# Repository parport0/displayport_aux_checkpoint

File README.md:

# displayport\_aux\_checkpoint 

An RP2040-powered box to be plugged between your computer and the monitor.

See also:

* [dvi_i2c_checkpoint](https://github.com/parport0/dvi_i2c_checkpoint)
* [ddcci_injector](https://github.com/parport0/ddcci_injector)
* [ddcci_dongle](https://github.com/parport0/ddcci_dongle)

Made to be manufactured at JLCPCB,

* JLC04161H-7628
* NanYa NP-155F

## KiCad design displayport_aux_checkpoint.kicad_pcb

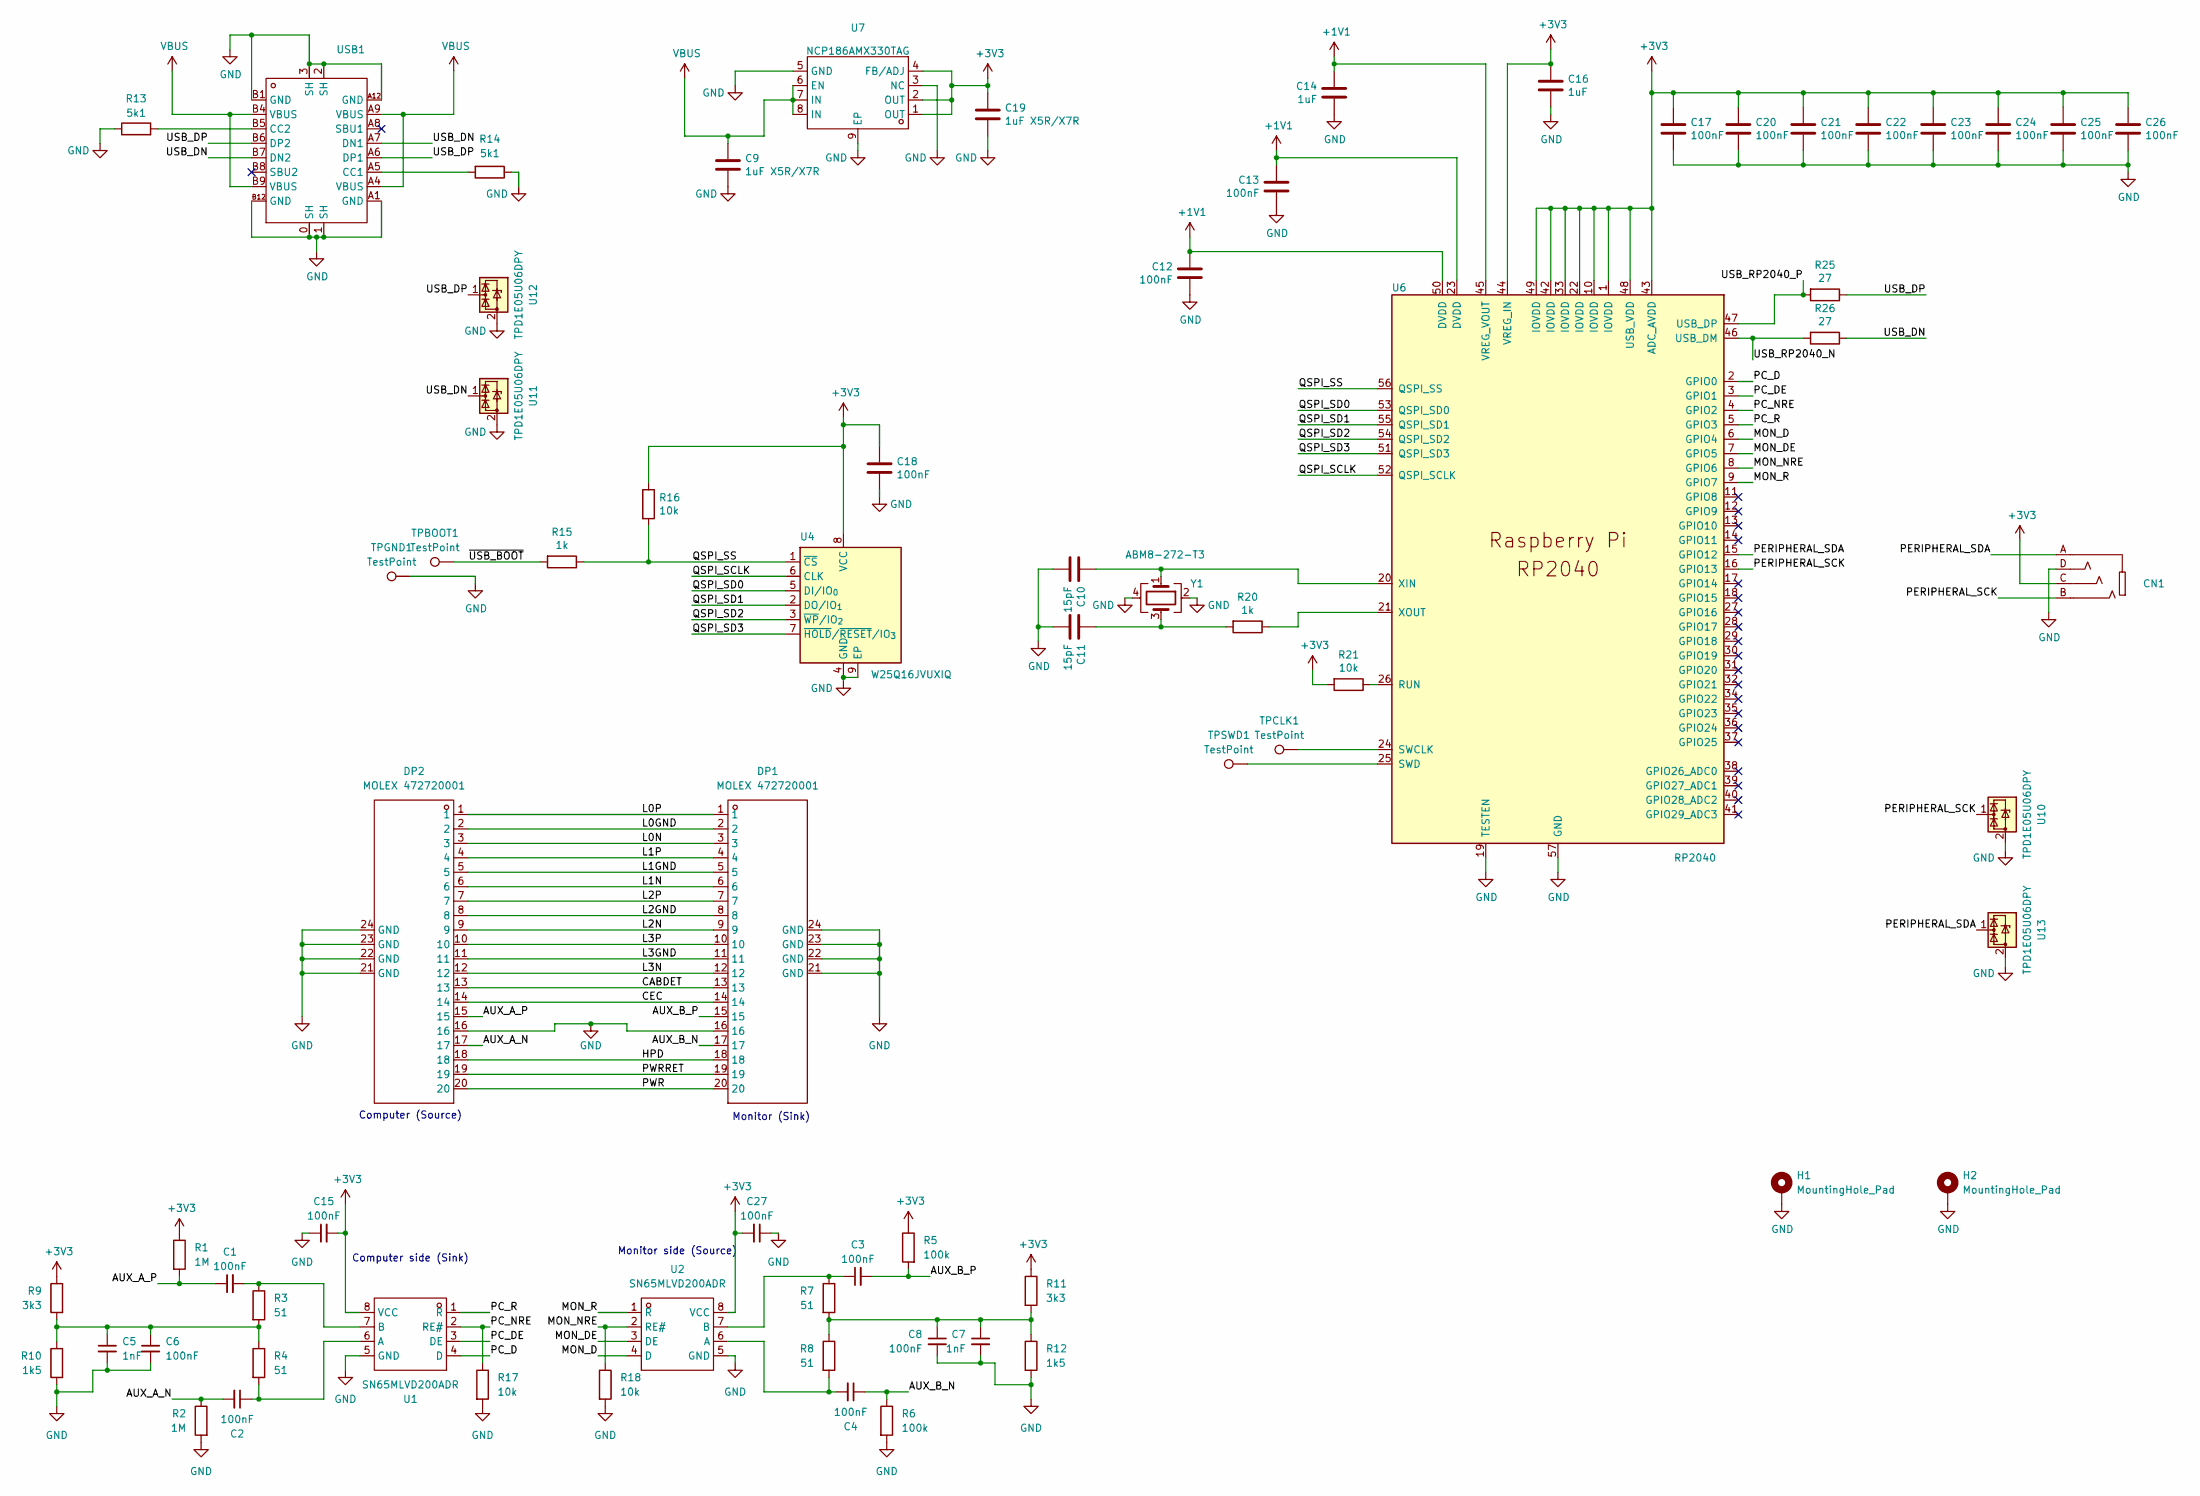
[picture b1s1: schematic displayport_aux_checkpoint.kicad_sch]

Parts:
C1, C2, C3, C4, C15, C27: 100nF; C_0402_1005Metric; Voltage 1kV; Tolerance 100%; LCSC Part C105883
C5, C7: 1nF; C_0402_1005Metric; LCSC Part C126532
C6, C8: 100nF; C_0603_1608Metric; LCSC Part C1591
C9, C19: 1uF X5R/X7R; C_0805_2012Metric; LCSC Part C28323
C10, C11: 15pF; C_0402_1005Metric; LCSC Part C1548
C12, C13, C17, C18, C20, C21, C22, C23, C24, C25, C26: 100nF; C_0402_1005Metric; LCSC Part C105883
C14, C16: 1uF; C_0402_1005Metric; LCSC Part C52923
CN1: AUDIO-TH_PJ-320A-4P-DIP; Manufacturer Part PJ-320A-4P DIP; LCSC Part Name 3.5mm耳机座
DP1, DP2: MOLEX 472720001; CONN-SMD_472720001; Manufacturer Part 472720001; LCSC Part Name 1.0mm间距显示端口插座组件
H1, H2: MountingHole_Pad; MountingHole_2.2mm_M2_Pad
R1, R2: 1M; R_0603_1608Metric; LCSC Part C107698
R3, R4, R7, R8: 51; R_0402_1005Metric; LCSC Part C853312
R5, R6: 100k; R_0603_1608Metric; LCSC Part C14675
R9, R11: 3k3; R_0402_1005Metric; LCSC Part C137992
R10, R12: 1k5; R_0402_1005Metric; LCSC Part C114451
R13, R14: 5k1; R_0402_1005Metric; LCSC Part C25905
R15, R20: 1k; R_0402_1005Metric; LCSC Part C11702
R16, R17, R18, R21: 10k; R_0402_1005Metric; LCSC Part C60490
R25, R26: 27; R_0402_1005Metric; LCSC Part C137890
TPBOOT1: TestPoint; TestPoint_Pad_D1.5mm
TPCLK1: TestPoint; TestPoint_Pad_D1.5mm
TPGND1: TestPoint; TestPoint_Pad_D1.5mm
TPSWD1: TestPoint; TestPoint_Pad_D1.5mm
U1, U2: SN65MLVD200ADR; SOIC-8_L5.0-W4.0-P1.27-LS6.0-BL; Manufacturer Part SN65MLVD200ADR; LCSC Part Name SN65MLVD200A 多点LVDS驱动器和接收器
U4: W25Q16JVUXIQ; Winbond_USON-8-1EP_3x2mm_P0.5mm_EP0.2x1.6mm; LCSC Part C2843335
U6: RP2040; QFN-56-1EP_7x7mm_P0.4mm_EP3.2x3.2mm; LCSC Part C2040
U7: XDFN-8_L1.6-W1.2-P0.40-BL-EP; Manufacturer Part NCP186AMX330TAG; LCSC Part Name NCP186AMX330TAG
U10, U11, U12, U13: TPD1E05U06DPY; Texas_DPY0002A_0.6x1mm_P0.65mm; LCSC Part C436349
USB1: USB-C_SMD-TYPE-C-31-M-12; LCSC Part Name Type-C 母 卧贴
Y1: ABM8-272-T3; Crystal_SMD_3225-4Pin_3.2x2.5mm; LCSC Part C20625731

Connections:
+1V1: C12.1, C13.1, C14.1, U6.23 (DVDD), U6.45 (VREG_VOUT), U6.50 (DVDD)
+3V3: C15.2, C16.1, C17.1, C18.1, C19.1, C20.1, C21.1, C22.1, C23.1, C24.1, C25.1, C26.1, C27.2, CN1.C, R1.1, R5.1, R9.1, R11.1, R16.1, R21.2, U1.8 (VCC), U2.8 (VCC), U4.8 (VCC), U6.1 (IOVDD), U6.10 (IOVDD), U6.22 (IOVDD), U6.33 (IOVDD), U6.42 (IOVDD), U6.43 (ADC_AVDD), U6.44 (VREG_IN), U6.48 (USB_VDD), U6.49 (IOVDD), U7.1 (OUT), U7.2 (OUT), U7.4 (FB/ADJ)
/AUX_A_N: C2.2, DP2.17, R2.1
/AUX_A_P: C1.1, DP2.15, R1.2
/AUX_B_N: C4.1, DP1.17, R6.1
/AUX_B_P: C3.2, DP1.15, R5.2
/CABDET: DP1.13, DP2.13
/CEC: DP1.14, DP2.14
/HPD: DP1.18, DP2.18
/L0GND: DP1.2, DP2.2
/L0N: DP1.3, DP2.3
/L0P: DP1.1, DP2.1
/L1GND: DP1.5, DP2.5
/L1N: DP1.6, DP2.6
/L1P: DP1.4, DP2.4
/L2GND: DP1.8, DP2.8
/L2N: DP1.9, DP2.9
/L2P: DP1.7, DP2.7
/L3GND: DP1.11, DP2.11
/L3N: DP1.12, DP2.12
/L3P: DP1.10, DP2.10
/MON_D: U2.4 (D), U6.6 (GPIO4)
/MON_DE: U2.3 (DE), U6.7 (GPIO5)
/MON_NRE: R18.1, U2.2 (RE#), U6.8 (GPIO6)
/MON_R: U2.1 (R), U6.9 (GPIO7)
/PC_D: U1.4 (D), U6.2 (GPIO0)
/PC_DE: U1.3 (DE), U6.3 (GPIO1)
/PC_NRE: R17.1, U1.2 (RE#), U6.4 (GPIO2)
/PC_R: U1.1 (R), U6.5 (GPIO3)
/PERIPHERAL_SCK: CN1.B, U6.16 (GPIO13), U10.1 (I/O)
/PERIPHERAL_SDA: CN1.A, U6.15 (GPIO12), U13.1 (I/O)
/PWR: DP1.20, DP2.20
/PWRRET: DP1.19, DP2.19
/QSPI_SCLK: U4.6 (CLK), U6.52 (QSPI_SCLK)
/QSPI_SD0: U4.5 (DI/IO_{0}), U6.53 (QSPI_SD0)
/QSPI_SD1: U4.2 (DO/IO_{1}), U6.55 (QSPI_SD1)
/QSPI_SD2: U4.3 (~WP/IO_{2}), U6.54 (QSPI_SD2)
/QSPI_SD3: U4.7 (~HOLD/~RESET/IO_{3}), U6.51 (QSPI_SD3)
/QSPI_SS: R15.1, R16.2, U4.1 (~CS), U6.56 (QSPI_SS)
/USB_DN: R26.1, U11.1 (I/O), USB1.A7 (DN1), USB1.B7 (DN2)
/USB_DP: R25.1, U12.1 (I/O), USB1.A6 (DP1), USB1.B6 (DP2)
/USB_RP2040_N: R26.2, U6.46 (USB_DM)
/USB_RP2040_P: R25.2, U6.47 (USB_DP)
/~USB_BOOT: R15.2, TPBOOT1.1; also elsewhere on the board
GND: C5.2, C6.2, C7.2, C8.2, C9.2, C10.2, C11.2, C12.2, C13.2, C14.2, C15.1, C16.2, C17.2, C18.2, C19.2, C20.2, C21.2, C22.2, C23.2, C24.2, C25.2, C26.2, C27.1, CN1.D, DP1.16, DP1.21 (GND), DP1.22 (GND), DP1.23 (GND), DP1.24 (GND), DP2.16, DP2.21 (GND), DP2.22 (GND), DP2.23 (GND), DP2.24 (GND), H1.1 (1_1), H2.1 (1_1), R2.2, R6.2, R10.2, R12.2, R13.1, R14.1, R17.2, R18.2, TPGND1.1, U1.5 (GND), U2.5 (GND), U4.4 (GND), U4.9 (EP), U6.19 (TESTEN), U6.57 (GND), U7.3 (NC), U7.5 (GND), U7.9 (EP), U10.2 (GND), U11.2 (GND), U12.2 (GND), U13.2 (GND), USB1.0 (SH), USB1.1 (SH), USB1.2 (SH), USB1.3 (SH), USB1.A1 (GND), USB1.A12 (GND), USB1.B1 (GND), USB1.B12 (GND), Y1.2, Y1.4; also elsewhere on the board
unnamed: C5.1, C6.1, R3.2, R4.1, R9.2, R10.1
unnamed: C7.1, C8.1, R7.2, R8.1, R11.2, R12.1
unnamed: C11.1, R20.2, Y1.3
unnamed: C2.1, R4.2, U1.6 (A)
unnamed: C1.2, R3.1, U1.7 (B)
unnamed: C4.2, R8.2, U2.6 (A)
unnamed: C3.1, R7.1, U2.7 (B)
unnamed: R21.1, U6.26 (RUN)
unnamed 53: TPCLK1.1, U6.24 (SWCLK); also elsewhere on the board
unnamed 54: TPSWD1.1, U6.25 (SWD); also elsewhere on the board
unnamed: C10.1, U6.20 (XIN), Y1.1
unnamed: R20.1, U6.21 (XOUT)
unnamed: R14.2, USB1.A5 (CC1)
unnamed: R13.2, USB1.B5 (CC2)
VBUS: C9.1, U7.6 (EN), U7.7 (IN), U7.8 (IN), USB1.A4 (VBUS), USB1.A9 (VBUS), USB1.B4 (VBUS), USB1.B9 (VBUS)

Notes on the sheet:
Computer side (Sink)
Computer (Source)
Monitor side (Source)
Monitor (Sink)

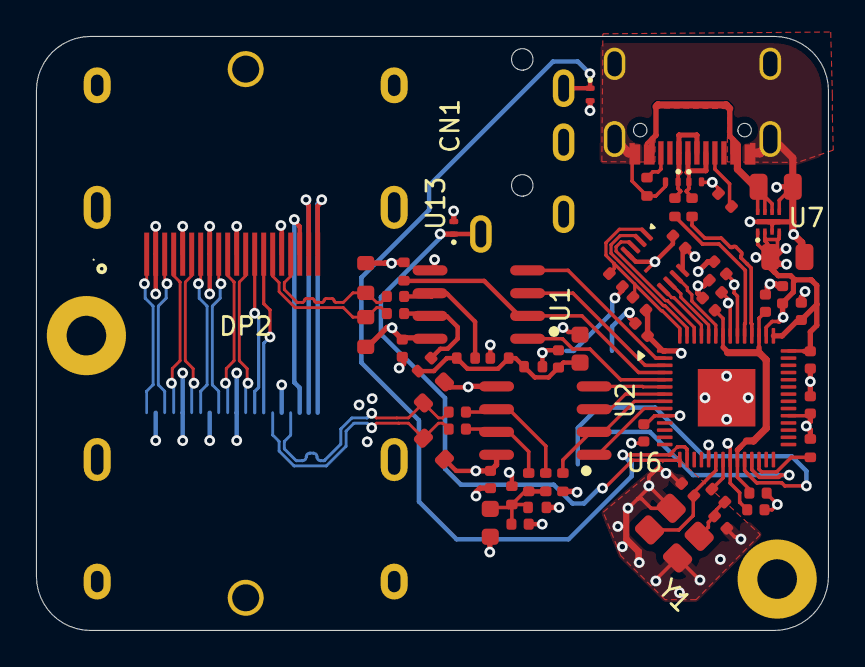
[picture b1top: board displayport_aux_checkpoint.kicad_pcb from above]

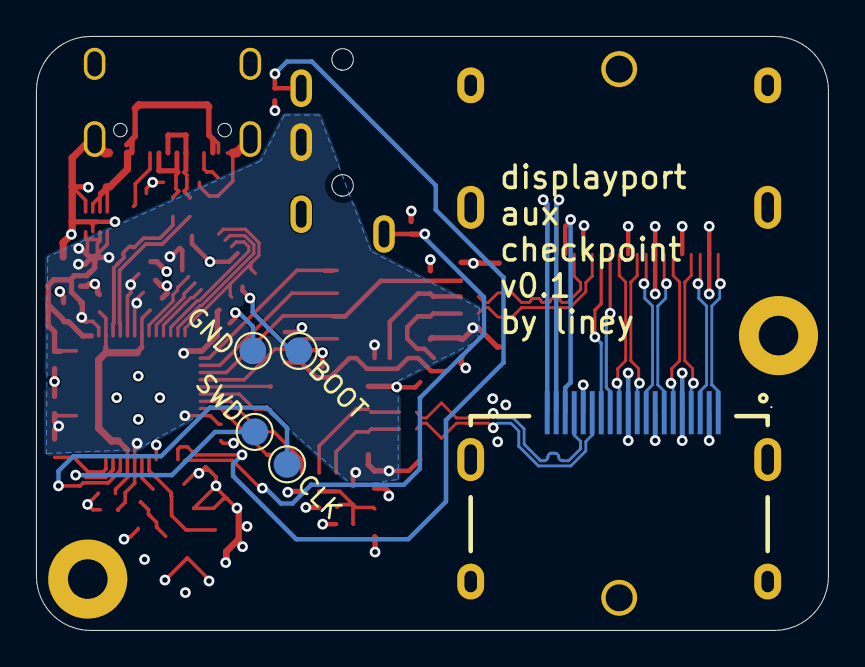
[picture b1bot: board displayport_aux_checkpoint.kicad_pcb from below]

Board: 4 copper layers, 44.0 x 33.0 mm, 69 parts (5 on the bottom side), 60 nets.

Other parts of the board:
BOOT: TestPoint; TestPoint_Pad_D1.5mm
CLK: TestPoint; TestPoint_Pad_D1.5mm
GND: TestPoint; TestPoint_Pad_D1.5mm
SWD: TestPoint; TestPoint_Pad_D1.5mm

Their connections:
/~USB_BOOT: BOOT.1 (1_1); also elsewhere on the board
GND: GND.1 (1_1); also elsewhere on the board
unnamed 53: CLK.1 (1_1); also elsewhere on the board
unnamed 54: SWD.1 (1_1); also elsewhere on the board
